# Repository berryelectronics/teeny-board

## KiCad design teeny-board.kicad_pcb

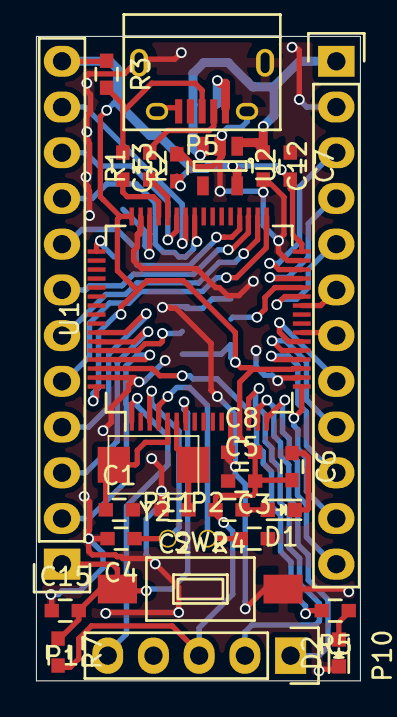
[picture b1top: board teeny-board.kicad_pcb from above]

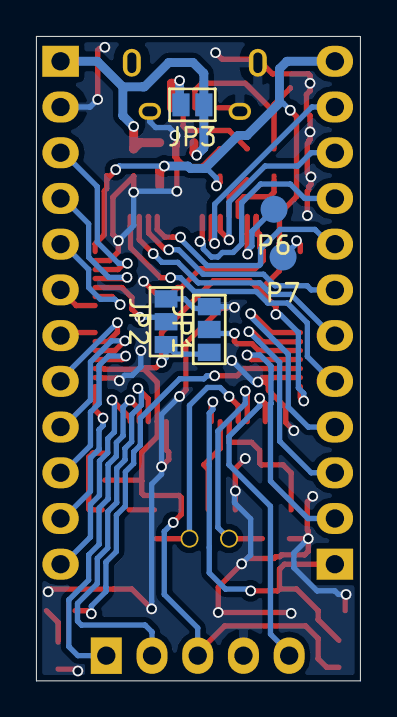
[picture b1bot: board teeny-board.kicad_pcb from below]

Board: 2 copper layers, 18.0 x 35.8 mm, 34 parts (5 on the bottom side), 43 nets.

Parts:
C1, C2, C3, C4: pf; C_0603
C5, C12, C13: 1uF; C_0603
C6, C7, C15: 100nF; C_0603
C8: 10nF; C_0603
D1, D2: Led_Small; LED_0603
JP1, JP2: JUMPER3; GS3
JP3: Jumper_NC_Small; GS2
P1, P3: CONN_01X12; Pin_Header_Straight_1x12
P2, P11: CONN_01X01; Measurement_Point_Round-TH_Small
P5: USB_OTG; USB_Micro-B
P6, P7: PAD; Measurement_Point_Round-SMD-Pad_Small
P10: CONN_01X05; Pin_Header_Straight_1x05
R1, R2: 22R; C_0603
R3: 150K; C_0603
R4, R5: 1K; C_0603
R7: 10K; C_0603
SW2: SW_PUSH; SW_SPST_FSMSM
U1: STM32F103Rxxx; LQFP-64_10x10mm_Pitch0.5mm
U2: AP2112K-3.3TRG1; SOT-23-5
Y2: 8Mhz; 2P-5032

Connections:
+3V3: C5.2, C6.2, C7.2, C8.2, C13.1, JP1.1, JP2.1, P1.12, P10.3, R3.1, R4.2, R7.2, U1.13, U1.19, U1.32, U1.48, U1.64, U2.5
/BOOT0: JP1.2, U1.60
/BOOT1: JP2.2, U1.28
/PA0: P10.2, U1.14
/PA1: P10.1, U1.15
/PA2: P3.12, U1.16
/PA3: P3.11, U1.17
/PA4: P3.10, U1.20
/PA5: P3.9, U1.21
/PA6: P3.8, U1.22
/PA7: P3.7, U1.23
/PA8: P1.9, U1.41
/PA9: P1.11, U1.42
/PA10: P1.10, U1.43
/PB0: P3.6, U1.26
/PB1: P3.5, U1.27
/PB6: P1.4, U1.58
/PB7: P1.3, U1.59
/PB8: P1.2, U1.61
/PB10: P3.4, U1.29
/PB11: P3.3, U1.30
/PB12: P1.5, U1.33
/PB13: P1.6, U1.34
/PB14: P1.7, U1.35
/PB15: P1.8, U1.36
/RST: C15.2, P1.1, R7.1, SW2.1, U1.7
/SWCLK: P7.1, U1.49
/SWDIO: P6.1, U1.46
/USBD+: R2.2, U1.45
/USBD-: R1.1, U1.44
/USBDR+: P5.3, R2.1, R3.2
/USBDR-: P5.2, R1.2
/USR_LED: R5.2, U1.62
/VBAT: P10.5, U1.1
GND: C1.2, C2.2, C3.2, C4.2, C5.1, C6.1, C7.1, C8.1, C12.2, C13.2, C15.1, D1.1, D2.1, JP1.3, JP2.3, P3.2, P5.5, P5.6, P10.4, SW2.2, U1.12, U1.18, U1.31, U1.47, U1.63, U2.2
unnamed: C1.1, U1.5, Y2.1
unnamed: C2.1, U1.6, Y2.2
unnamed: C3.1, P2.1, U1.4
unnamed: C4.1, P11.1, U1.3
unnamed: D1.2, R4.1
unnamed: D2.2, R5.1
VCC: C12.1, JP3.1, P3.1, U2.1, U2.3
VDD: JP3.2, P5.1

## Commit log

2016-08-06 :confetti_ball: Added .gitattributes & .gitignore files
2016-08-07 added kicad project and specs table
2016-08-08 first revision
2016-08-08 corrected gerbers
2016-08-08 changed outline naming
